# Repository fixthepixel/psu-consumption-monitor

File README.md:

# PSU Consumption Monitor

High-side current and power monitoring board for **ATX power supplies**.  
This project allows measuring real-time **current, voltage, and power consumption**
on major ATX rails for diagnostics, testing, and educational purposes.

Created and documented by **FixThePixel**.

---

## ✨ Features

- High-side current sensing using precision shunt resistors
- Multi-rail monitoring:
  - +12 V
  - +5 V
  - +3.3 V
  - +5 VSB
- Bus voltage and current measurement via **INA3221**
- Inline ATX connector design
- MicroPython-based firmware
- Project-local KiCad symbols and footprints
- Clean, GitHub-friendly project structure

---

## 📐 Measurements

Per-rail power is calculated as:

```
Power (W) = Voltage (V) × Current (A)
```

Total system power can be derived by summing all monitored rails.

---

## 🧰 Tools & Requirements

### Hardware / CAD

- **KiCad 9.x** (tested)
- Standard KiCad libraries (symbols, footprints, 3D models)

---

## 🧩 3D Models

This repository **does not include third-party 3D models**.

- Standard KiCad 3D models are referenced via `${KICAD*_3DMODEL_DIR}`
- Third-party 3D models shown in videos are **not bundled**
- Optional model links may be provided separately

---

## 🧪 Fabrication (Gerbers)

Generated Gerber files are included for **non-commercial manufacturing only**.

See `gerber/README.md` for fabrication-specific notes and licensing.

---

## 🔌 Firmware

The `/firmware` directory contains MicroPython firmware for the monitor.

### Firmware Installation Guide

1.  **Board**
   
    MicroPython firmware must be installed on the target board (RP2040).

2.  **Installation**
   
    Copy all `*.py` files from `/firmware` directory into the root directory of the MicroPython device.

3.  **Third-party dependencies**
   
    The firmware depends on the ILI9341 display driver and font files from:

    - `https://github.com/jeffmer/micropython-ili9341`

    Required files:
      - ili934xnew.py
      - glcdfont.py
      - tt14.py
      - tt24.py

    These files are used unmodified and retain their original MIT license.
    They must also be copied to the root directory of the MicroPython device.

---

## 📜 License

This project is licensed under:

**Creative Commons Attribution–NonCommercial 4.0 International (CC BY-NC 4.0)**

Commercial use, manufacturing, or sale is **not permitted** without explicit permission.

https://creativecommons.org/licenses/by-nc/4.0/

---

## ⚠️ Disclaimer

This project is intended for **development, diagnostics, and educational use**.

Working with ATX power supplies involves **high current and potentially hazardous voltages**.
Use at your own risk.

---

## 👤 Author

**FixThePixel**  
YouTube: https://www.youtube.com/@FixThePixel

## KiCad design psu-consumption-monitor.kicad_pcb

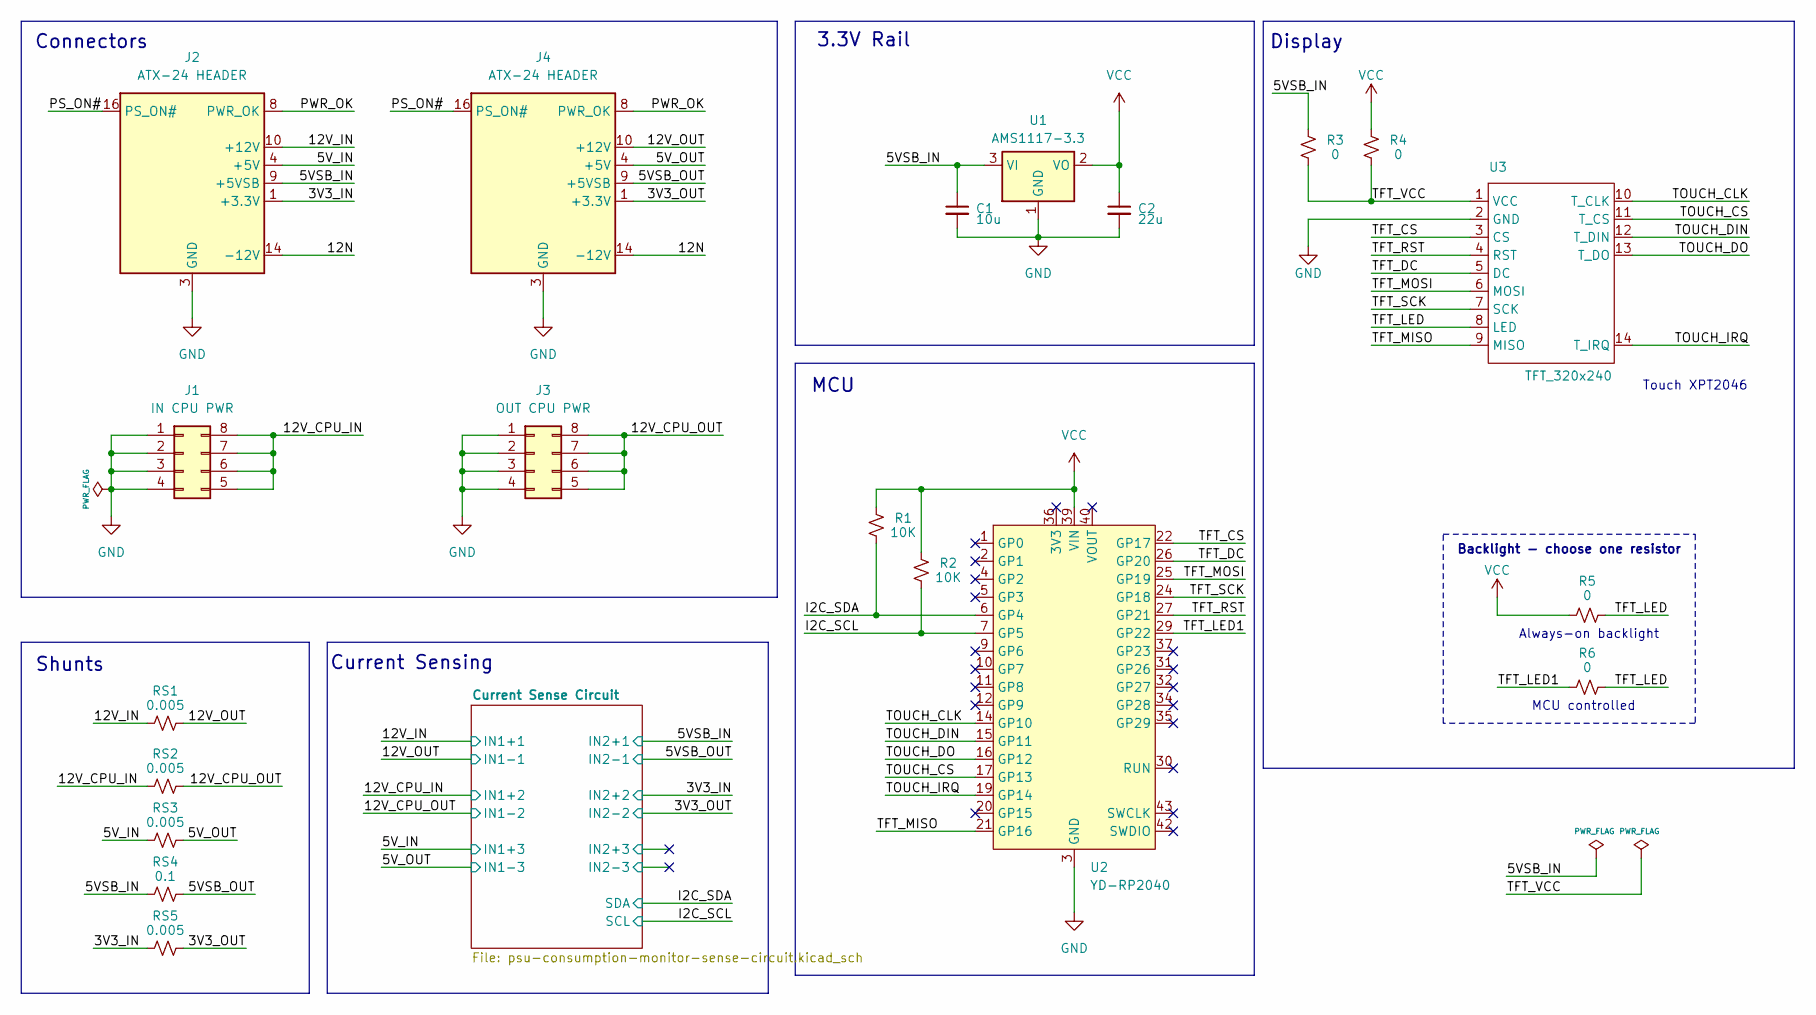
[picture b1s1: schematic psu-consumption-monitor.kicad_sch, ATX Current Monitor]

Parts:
C1: 10u; C_1206_3216Metric
C2: 22u; C_1206_3216Metric
J1: IN CPU PWR; Molex_Mini-Fit_Jr_5566-08A_2x04_P4.20mm_Vertical
J2, J4: ATX-24 HEADER; ATX-24-HEADER-HORIZONTAL
J3: OUT CPU PWR; Molex_Mini-Fit_Jr_5566-08A_2x04_P4.20mm_Vertical
R1, R2: 10K; R_0805_2012Metric
R3, R4, R5, R6: 0; R_0603_1608Metric
RS1, RS2, RS3, RS5: 0.005; R_2512_6332Metric
RS4: 0.1; R_2512_6332Metric
U1: AMS1117-3.3; SOT-223-3_TabPin2
U2: YD-RP2040
U3: TFT_320x240; TFT-320x240

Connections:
/3V3_IN: J2.1 (+3.3V), J2.2 (+3.3V), J2.12 (+3.3V), J2.13 (+3.3V), RS5.1; also elsewhere on the board
/3V3_OUT: J4.1 (+3.3V), J4.2 (+3.3V), J4.12 (+3.3V), J4.13 (+3.3V), RS5.2; also elsewhere on the board
/5VSB_IN: C1.1, J2.9 (+5VSB), R3.2, RS4.1, U1.3 (VI); also elsewhere on the board
/5VSB_OUT: J4.9 (+5VSB), RS4.2; also elsewhere on the board
/5V_IN: J2.4 (+5V), J2.6 (+5V), J2.21 (+5V), J2.22 (+5V), J2.23 (+5V), RS3.1; also elsewhere on the board
/5V_OUT: J4.4 (+5V), J4.6 (+5V), J4.21 (+5V), J4.22 (+5V), J4.23 (+5V), RS3.2; also elsewhere on the board
/12N: J2.14 (-12V), J4.14 (-12V)
/12V_CPU_IN: J1.5, J1.6, J1.7, J1.8, RS2.1; also elsewhere on the board
/12V_CPU_OUT: J3.5, J3.6, J3.7, J3.8, RS2.2; also elsewhere on the board
/12V_IN: J2.10 (+12V), J2.11 (+12V), RS1.1; also elsewhere on the board
/12V_OUT: J4.10 (+12V), J4.11 (+12V), RS1.2; also elsewhere on the board
/I2C_SCL: R2.1, U2.7 (GP5); also elsewhere on the board
/I2C_SDA: R1.1, U2.6 (GP4); also elsewhere on the board
/PS_ON#: J2.16 (PS_ON#), J4.16 (PS_ON#)
/PWR_OK: J2.8 (PWR_OK), J4.8 (PWR_OK)
/TFT_CS: U2.22 (GP17), U3.3 (CS)
/TFT_DC: U2.26 (GP20), U3.5 (DC)
/TFT_LED: R5.1, R6.1, U3.8 (LED)
/TFT_LED1: R6.2, U2.29 (GP22)
/TFT_MISO: U2.21 (GP16), U3.9 (MISO)
/TFT_MOSI: U2.25 (GP19), U3.6 (MOSI)
/TFT_RST: U2.27 (GP21), U3.4 (RST)
/TFT_SCK: U2.24 (GP18), U3.7 (SCK)
/TFT_VCC: R3.1, R4.1, U3.1 (VCC)
/TOUCH_CLK: U2.14 (GP10), U3.10 (T_CLK)
/TOUCH_CS: U2.17 (GP13), U3.11 (T_CS)
/TOUCH_DIN: U2.15 (GP11), U3.12 (T_DIN)
/TOUCH_DO: U2.16 (GP12), U3.13 (T_DO)
/TOUCH_IRQ: U2.19 (GP14), U3.14 (T_IRQ)
GND: C1.2, C2.2, J1.1, J1.2, J1.3, J1.4, J2.3 (GND), J2.5 (GND), J2.7 (GND), J2.15 (GND), J2.17 (GND), J2.18 (GND), J2.19 (GND), J2.24 (GND), J3.1, J3.2, J3.3, J3.4, J4.3 (GND), J4.5 (GND), J4.7 (GND), J4.15 (GND), J4.17 (GND), J4.18 (GND), J4.19 (GND), J4.24 (GND), U1.1 (GND), U2.3 (GND), U2.8 (GND), U2.13 (GND), U2.18 (GND), U2.23 (GND), U2.28 (GND), U2.33 (GND), U2.38 (GND), U2.44 (GND), U3.2 (GND); also elsewhere on the board
VCC: C2.1, R1.2, R2.2, R4.2, R5.2, U1.2 (VO), U2.39 (VIN); also elsewhere on the board

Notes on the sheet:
Current Sensing
Touch XPT2046
Shunts
3.3V Rail
Display
Backlight - choose one resistor
MCU controlled
Always-on backlight
Connectors
MCU

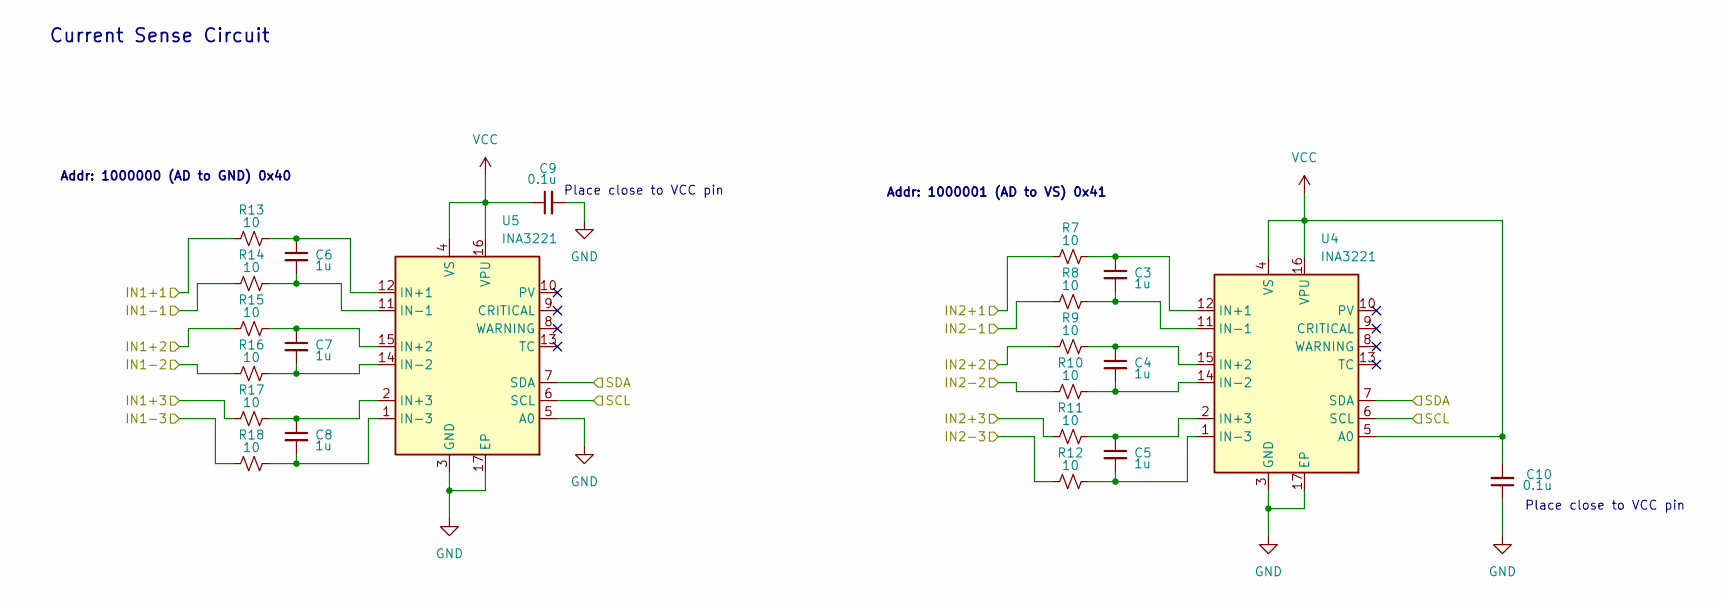
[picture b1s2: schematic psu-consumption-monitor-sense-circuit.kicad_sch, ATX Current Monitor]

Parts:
C3, C4, C5, C6, C7, C8: 1u; C_0603_1608Metric
C9, C10: 0.1u; C_0603_1608Metric
R7, R8, R9, R10, R11, R12, R13, R14, R15, R16, R17, R18: 10; R_0805_2012Metric
U4, U5: INA3221; Texas_RGV0016A_VQFN-16-1EP_4x4mm_P0.65mm_EP2.1x2.1mm

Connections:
/3V3_IN: R9.1; also elsewhere on the board
/3V3_OUT: R10.1; also elsewhere on the board
/5VSB_IN: R7.1; also elsewhere on the board
/5VSB_OUT: R8.1; also elsewhere on the board
/5V_IN: R17.1; also elsewhere on the board
/5V_OUT: R18.1; also elsewhere on the board
/12V_CPU_IN: R15.1; also elsewhere on the board
/12V_CPU_OUT: R16.1; also elsewhere on the board
/12V_IN: R13.1; also elsewhere on the board
/12V_OUT: R14.1; also elsewhere on the board
/Current Sense Circuit/IN2+3: R11.1
/Current Sense Circuit/IN2-3: R12.1
/I2C_SCL: U4.6 (SCL), U5.6 (SCL); also elsewhere on the board
/I2C_SDA: U4.7 (SDA), U5.7 (SDA); also elsewhere on the board
GND: C9.2, C10.1, U4.3 (GND), U4.17 (EP), U5.3 (GND), U5.5 (A0), U5.17 (EP); also elsewhere on the board
unnamed: C3.1, R7.2, U4.12 (IN+1)
unnamed: C4.1, R9.2, U4.15 (IN+2)
unnamed: C5.1, R11.2, U4.2 (IN+3)
unnamed: C3.2, R8.2, U4.11 (IN-1)
unnamed: C4.2, R10.2, U4.14 (IN-2)
unnamed: C5.2, R12.2, U4.1 (IN-3)
unnamed: C6.1, R13.2, U5.12 (IN+1)
unnamed: C7.1, R15.2, U5.15 (IN+2)
unnamed: C8.1, R17.2, U5.2 (IN+3)
unnamed: C6.2, R14.2, U5.11 (IN-1)
unnamed: C7.2, R16.2, U5.14 (IN-2)
unnamed: C8.2, R18.2, U5.1 (IN-3)
VCC: C9.1, C10.2, U4.4 (VS), U4.5 (A0), U4.16 (VPU), U5.4 (VS), U5.16 (VPU); also elsewhere on the board

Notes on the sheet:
Current Sense Circuit
Place close to VCC pin
Addr: 1000001 (AD to VS) 0x41
Addr: 1000000 (AD to GND) 0x40

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
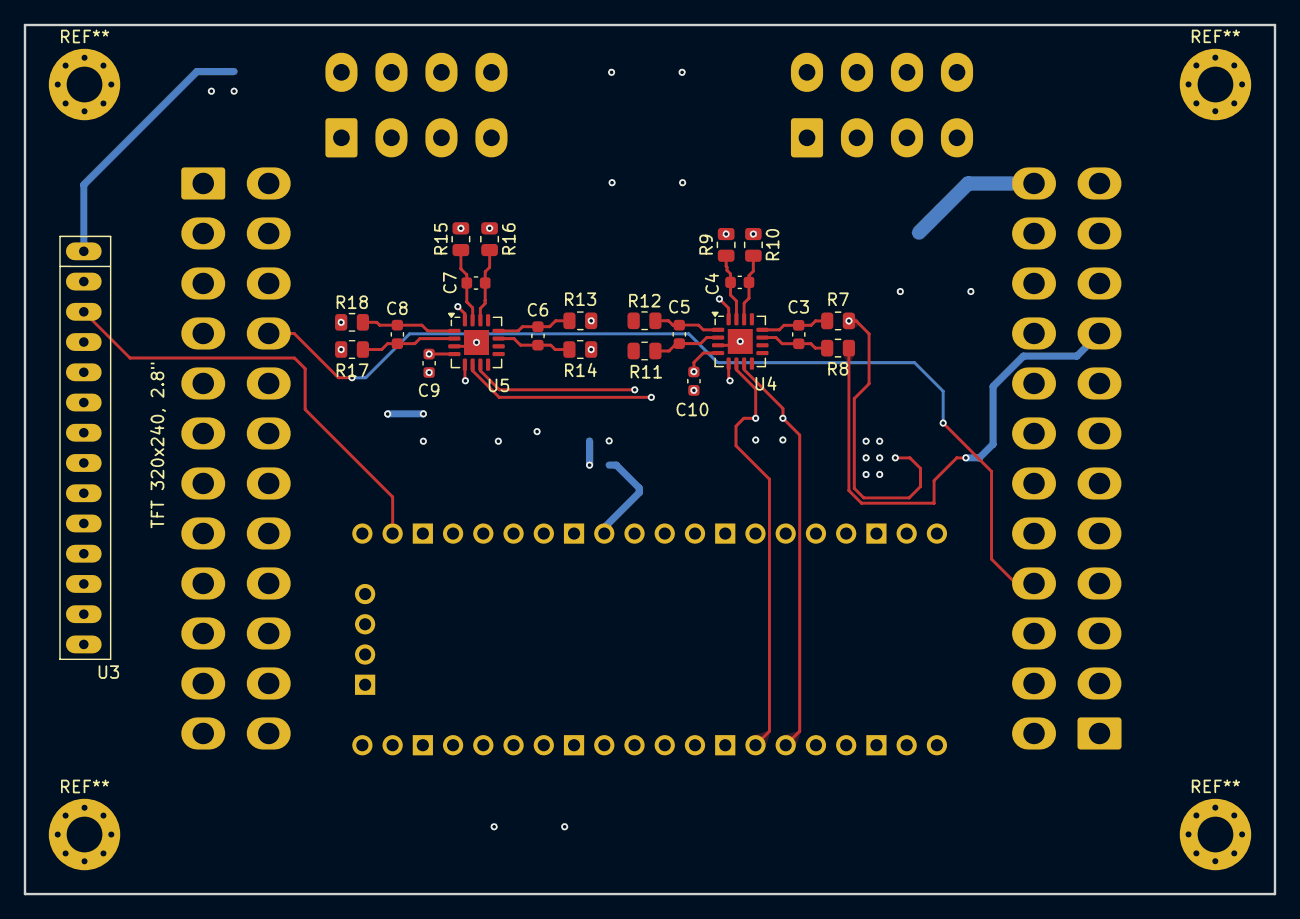
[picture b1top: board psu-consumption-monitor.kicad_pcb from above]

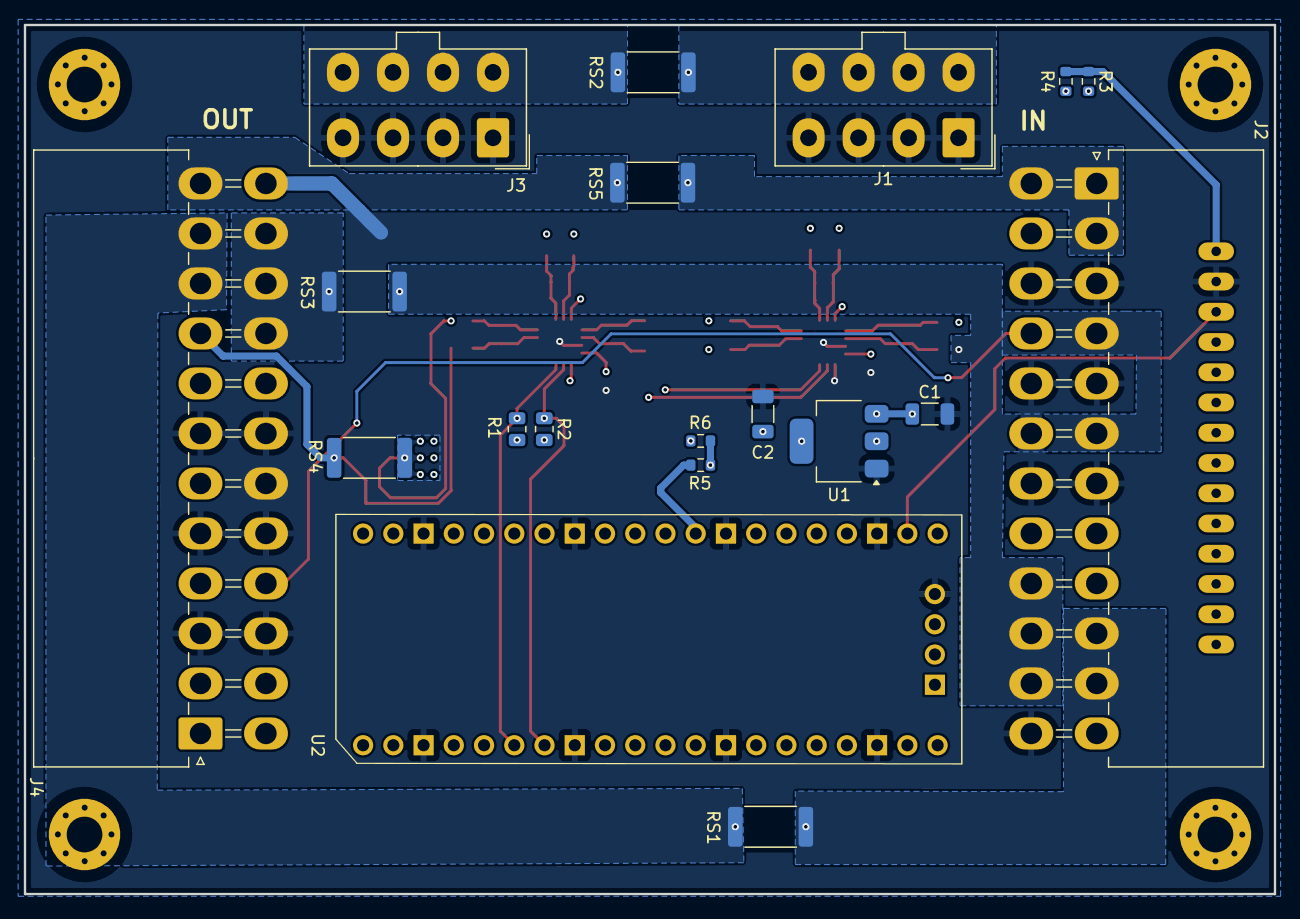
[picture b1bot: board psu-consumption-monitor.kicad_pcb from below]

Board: 4 copper layers, 105.0 x 73.0 mm, 42 parts (19 on the bottom side), 43 nets.

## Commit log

2025-12-27 Added firmware
2025-12-27 Added firmware installation guide to README.md
2026-06-24 Added serial output in a separate thread
2026-06-24 Added OBS overlay and serial bridge
